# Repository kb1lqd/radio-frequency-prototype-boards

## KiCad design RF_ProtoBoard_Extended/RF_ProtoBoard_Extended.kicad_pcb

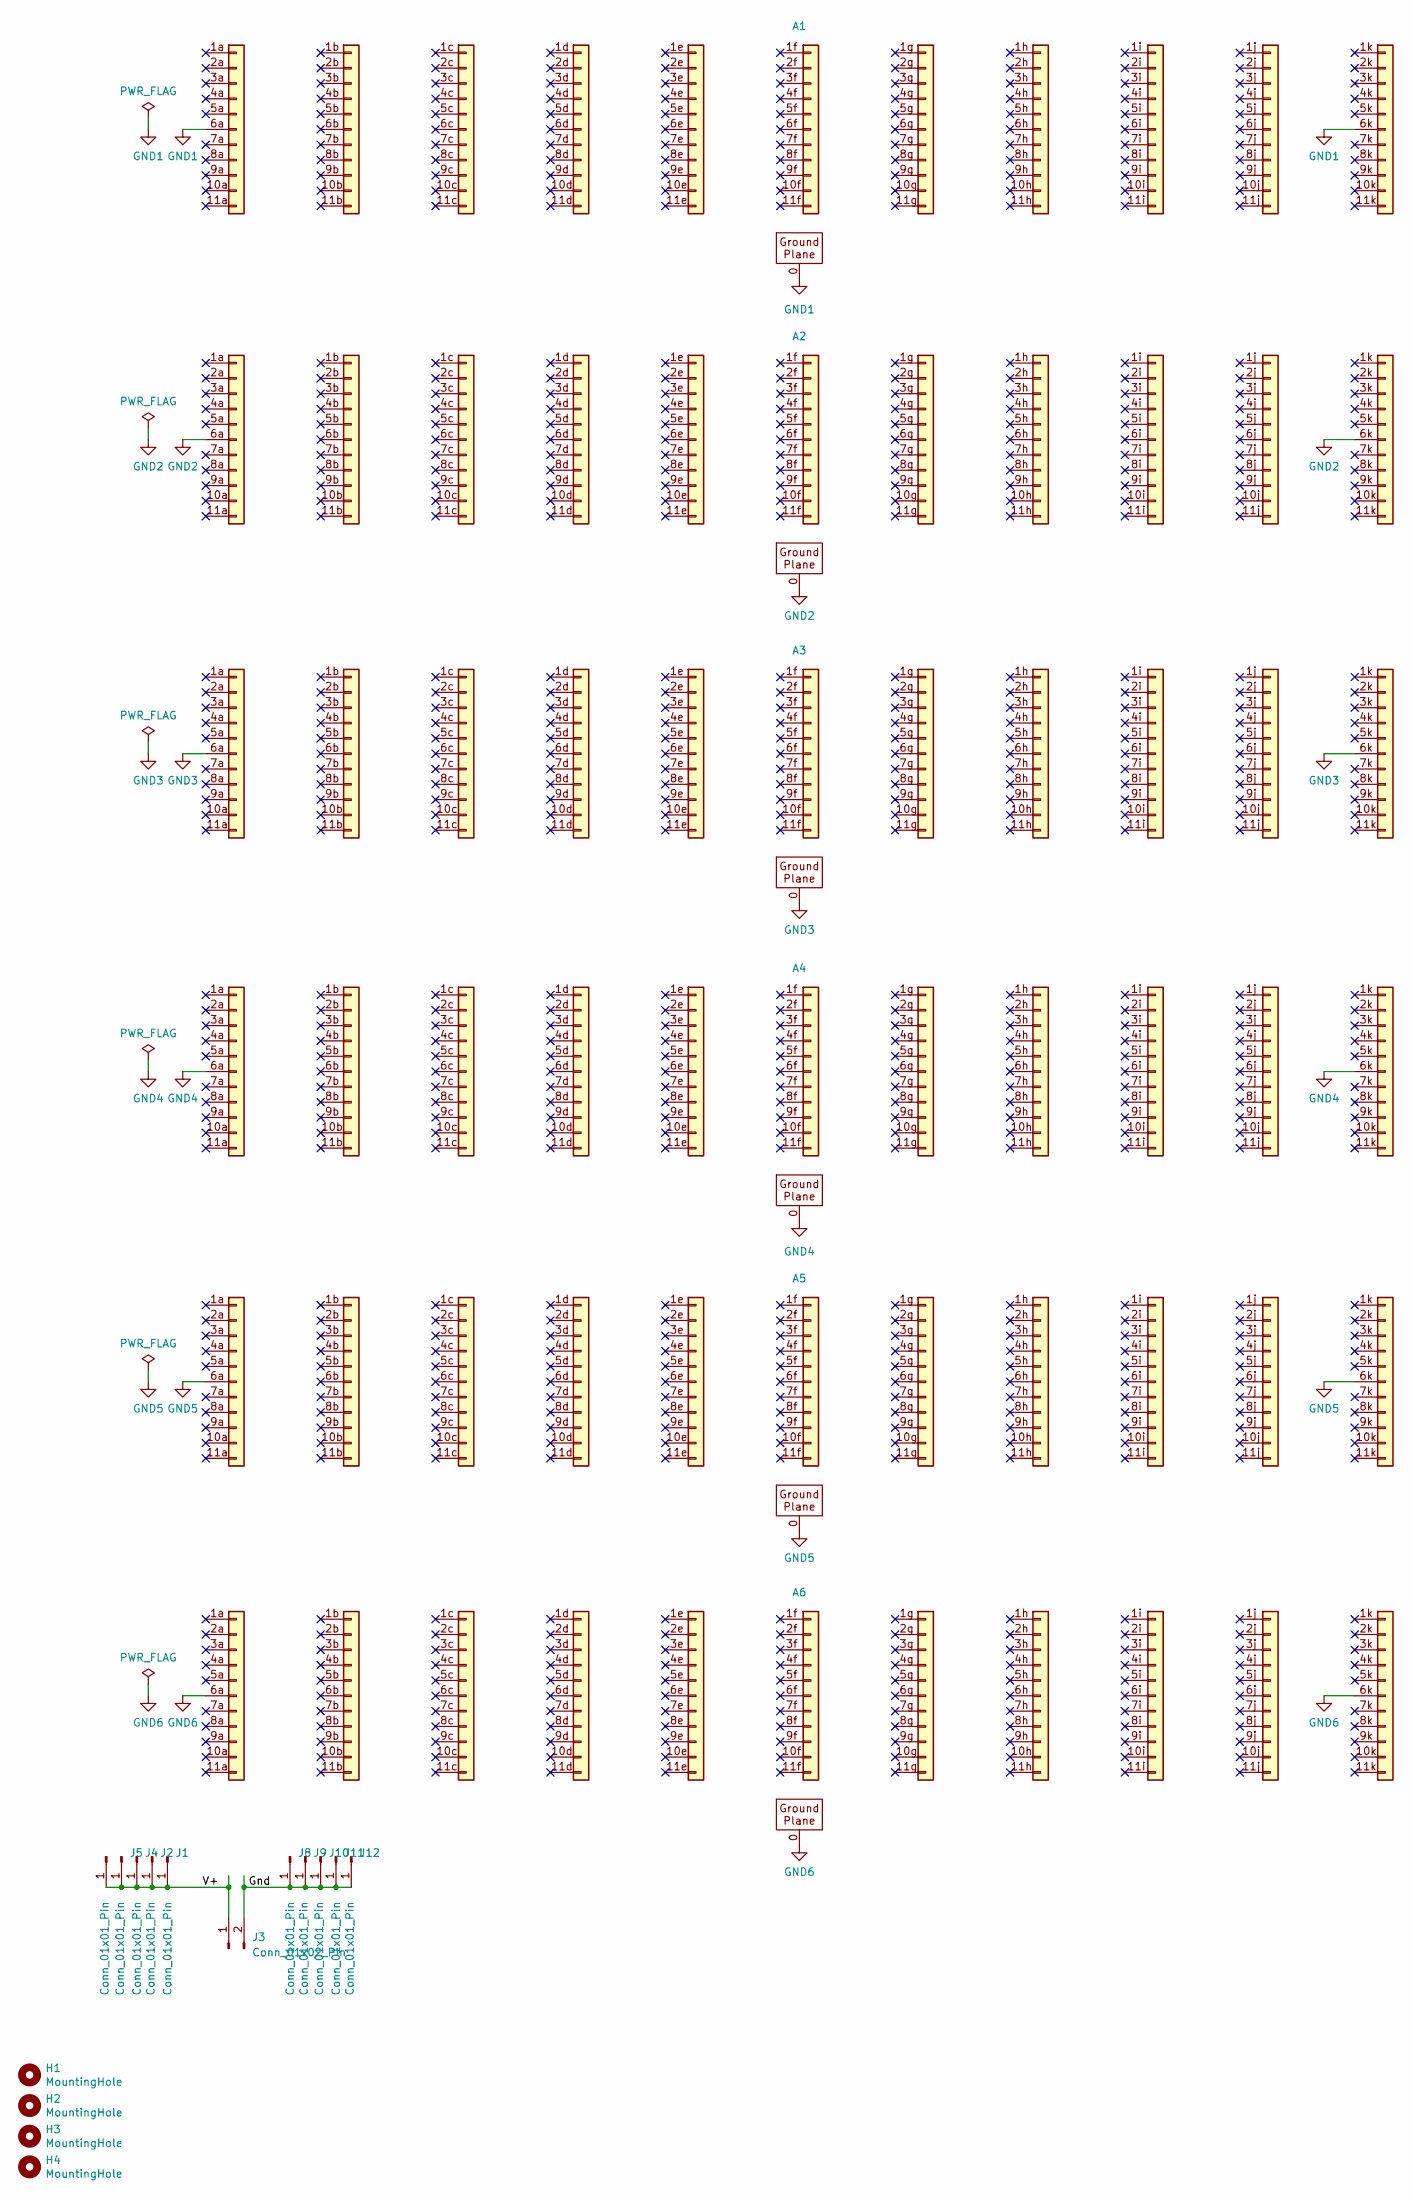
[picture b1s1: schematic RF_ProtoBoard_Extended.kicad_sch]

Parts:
A1, A2, A3, A4, A5, A6: GndRing_RF_ProtoBoard_Module
H1, H2, H3, H4: MountingHole; MountingHole_3.2mm_M3; Part Description M2.5 mounting hole
J1, J2, J4, J5, J6, J8, J9, J10, J11, J12: Conn_01x01_Pin; SolderWire-0.75sqmm_1x01_D1.25mm_OD2.3mm
J3: Conn_01x02_Pin; CONN_SD-43650-001_02_MOL

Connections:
/Gnd: J3.2, J8.1, J9.1, J10.1, J11.1, J12.1
/V+: J1.1, J2.1, J3.1, J4.1, J5.1, J6.1
GND1: A1.0 (Pin_Gnd), A1.6a, A1.6k
GND2: A2.0 (Pin_Gnd), A2.6a, A2.6k
GND3: A3.0 (Pin_Gnd), A3.6a, A3.6k
GND4: A4.0 (Pin_Gnd), A4.6a, A4.6k
GND5: A5.0 (Pin_Gnd), A5.6a, A5.6k
GND6: A6.0 (Pin_Gnd), A6.6a, A6.6k

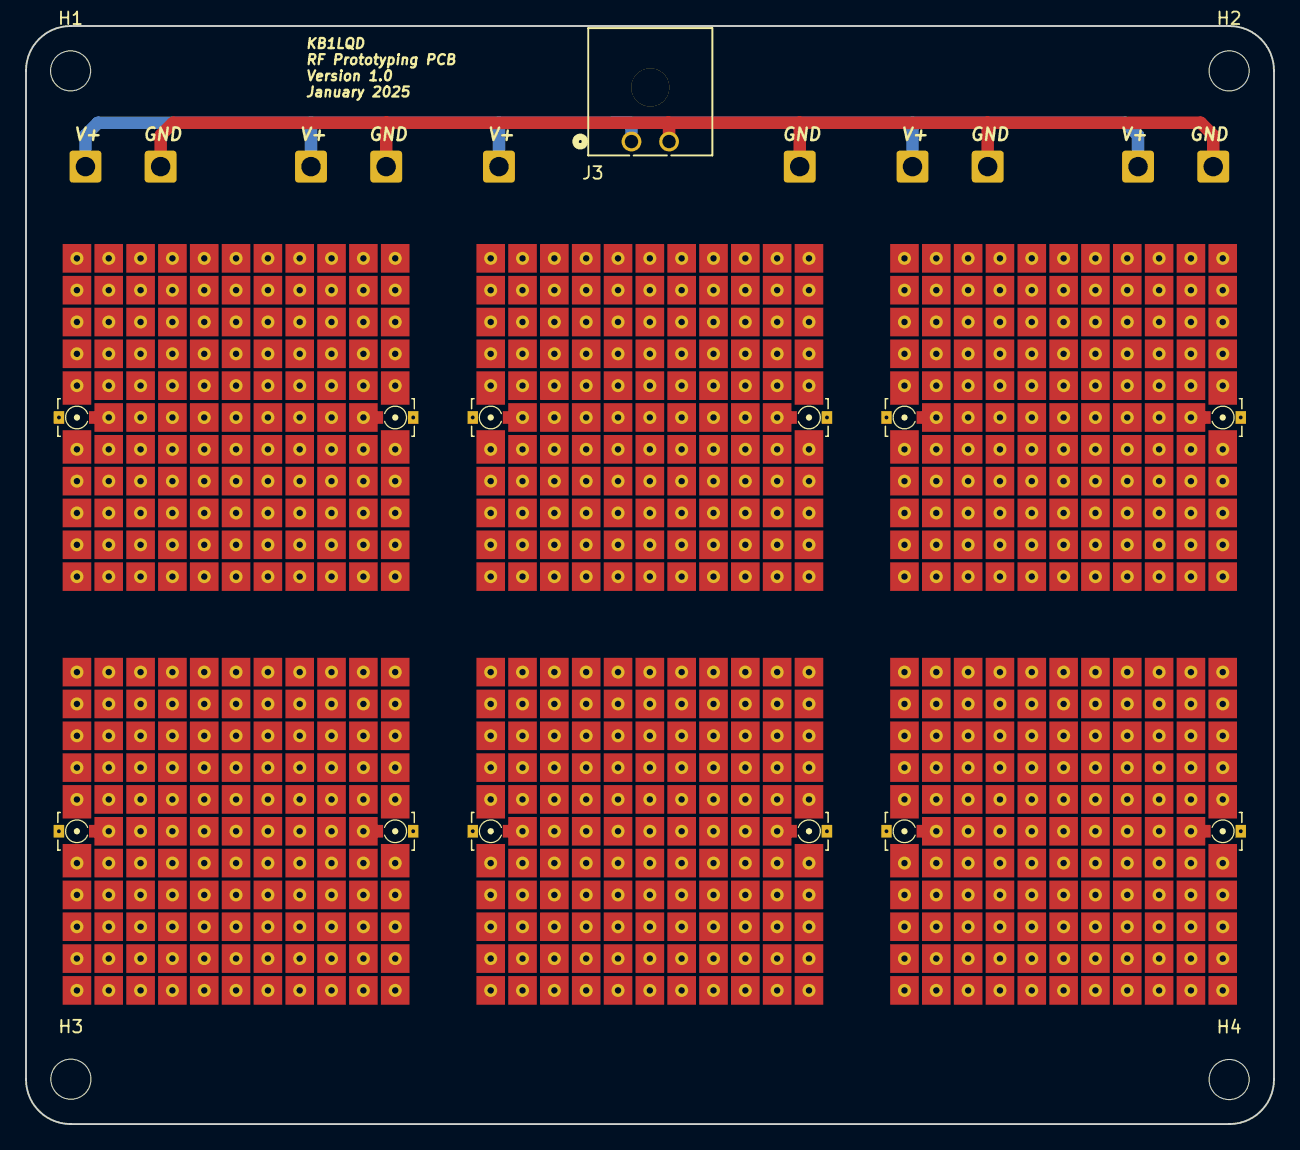
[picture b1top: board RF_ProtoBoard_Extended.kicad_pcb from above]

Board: 2 copper layers, 99.6 x 87.6 mm, 21 parts (0 on the bottom side), 8 nets.

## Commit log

2025-01-19 Basic update.
    Did basic power update. Would like to add an SOIC-8 or such of parts I normally use.
2025-01-19 Ready to output.
2025-01-20 Ordered.
